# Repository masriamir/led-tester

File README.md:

# LED Tester

This poject allows testing up to 16 LEDs at once in a 4X4 grid arrangement. A battery or 9V center-negative power supply can be used to power the circuit. A simple switch turns the LEDs on and off.

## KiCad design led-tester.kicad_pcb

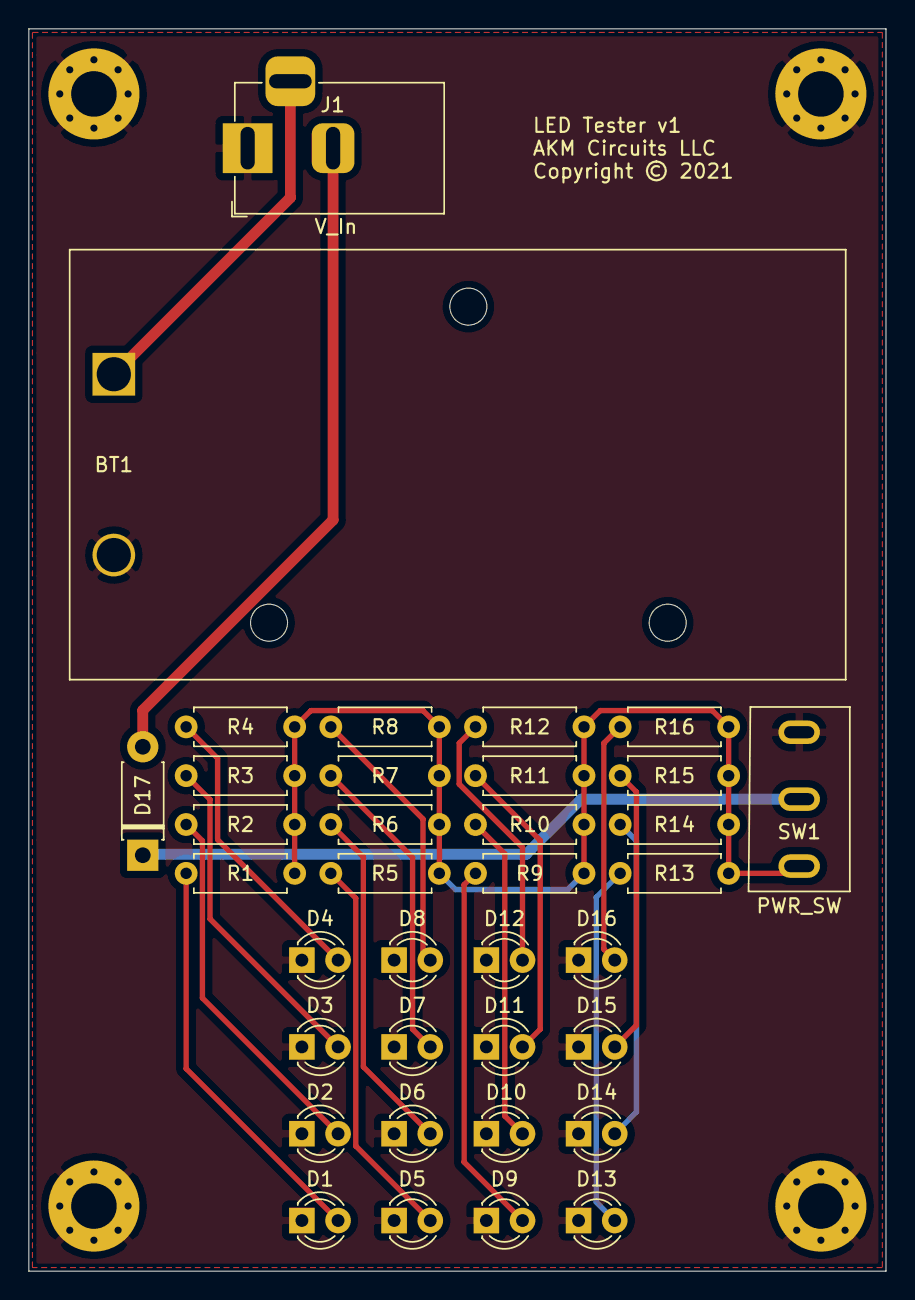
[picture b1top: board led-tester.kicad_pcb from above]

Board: 2 copper layers, 60.2 x 87.2 mm, 41 parts (1 on the bottom side), 21 nets.

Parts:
BT1: Battery; BatteryHolder_Eagle_12BH611-GR
D1, D2, D3, D4, D5, D6, D7, D8, D9, D10, D11, D12, D13, D14, D15, D16: LED; LED_D3.0mm
D17: 1N5817; D_DO-41_SOD81_P7.62mm_Horizontal
H1, H2, H3, H4: MountingHole_Pad; MountingHole_3.2mm_M3_Pad_Via
J1: V_In; BarrelJack_Horizontal
R1, R2, R3, R4, R5, R6, R7, R8, R9, R10, R11, R12, R13, R14, R15, R16: 4K7; R_Axial_DIN0207_L6.3mm_D2.5mm_P7.62mm_Horizontal
SW1: PWR_SW; Switch_SPDT
SYM1: SYM_AKM_Logo; Logo_800

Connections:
GND: BT1.2, D1.1, D2.1, D3.1, D4.1, D5.1, D6.1, D7.1, D8.1, D9.1, D10.1, D11.1, D12.1, D13.1, D14.1, D15.1, D16.1, H1.1, H2.1, H3.1, H4.1, J1.1, SW1.3
unnamed: BT1.1, J1.3
unnamed: D1.2, R1.1
unnamed: D2.2, R2.1
unnamed: D3.2, R3.1
unnamed: D4.2, R4.1
unnamed: D5.2, R5.1
unnamed: D6.2, R6.1
unnamed: D7.2, R7.1
unnamed: D8.2, R8.1
unnamed: D9.2, R9.1
unnamed: D10.2, R10.1
unnamed: D11.2, R11.1
unnamed: D12.2, R12.1
unnamed: D13.2, R13.1
unnamed: D14.2, R14.1
unnamed: D15.2, R15.1
unnamed: D16.2, R16.1
unnamed: D17.1, SW1.2
unnamed: D17.2, J1.2
VCC: R1.2, R2.2, R3.2, R4.2, R5.2, R6.2, R7.2, R8.2, R9.2, R10.2, R11.2, R12.2, R13.2, R14.2, R15.2, R16.2, SW1.1

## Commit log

2021-08-10 add initial draft
2021-08-10 add finalized draft schematic and pcb layout
2021-08-10 add gerber files for v1
2021-08-10 add BOM for v1
2021-08-10 adjust silkscreen placement
2021-08-10 add board dimensions
2021-08-10 update gerber files for v1
2021-08-10 add revision information to silkscreen
2021-08-12 add README.md
2021-08-12 add LICENSE and update information

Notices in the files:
led-tester.kicad_pcb:
License: CC-BY-SA-4.0
Copyright © 2021
